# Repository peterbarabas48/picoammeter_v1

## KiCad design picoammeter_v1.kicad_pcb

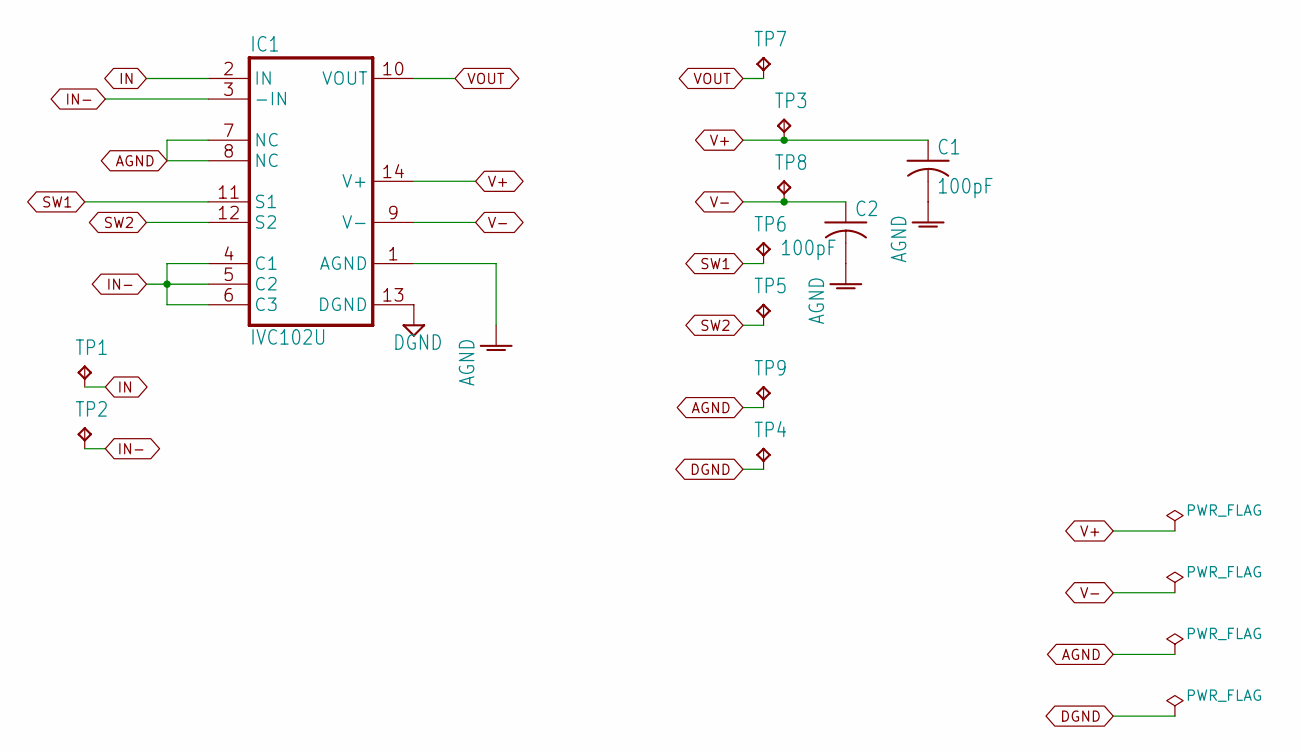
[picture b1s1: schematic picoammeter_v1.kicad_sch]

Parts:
C1, C2: 100pF; C0603; MPN GRM1885C1H101JA01D
IC1: IVC102U; SO14; MPN IVC102U
TP1, TP2, TP3, TP4, TP5, TP6, TP7, TP8, TP9: TPPAD1-13; P1-13

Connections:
AGND: C1.2, C2.2, IC1.1 (AGND), IC1.7 (NC), IC1.8 (NC), TP9.TP
DGND: IC1.13 (DGND), TP4.TP
IN: IC1.2 (IN), TP1.TP
IN-: IC1.3 (-IN), IC1.4 (C1), IC1.5 (C2), IC1.6 (C3), TP2.TP
SW1: IC1.11 (S1), TP6.TP
SW2: IC1.12 (S2), TP5.TP
V+: C1.1, IC1.14 (V+), TP3.TP
V-: C2.1, IC1.9 (V-), TP8.TP
VOUT: IC1.10 (VOUT), TP7.TP

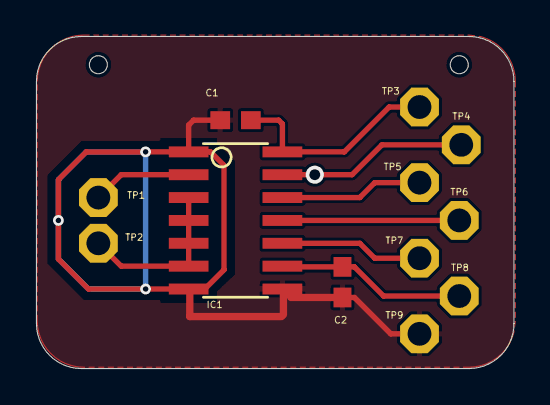
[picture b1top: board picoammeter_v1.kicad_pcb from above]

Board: 2 copper layers, 26.5 x 18.5 mm, 14 parts (0 on the bottom side), 9 nets.

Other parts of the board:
UNK_HOLE_0: dummyfp0
UNK_HOLE_1: dummyfp1
